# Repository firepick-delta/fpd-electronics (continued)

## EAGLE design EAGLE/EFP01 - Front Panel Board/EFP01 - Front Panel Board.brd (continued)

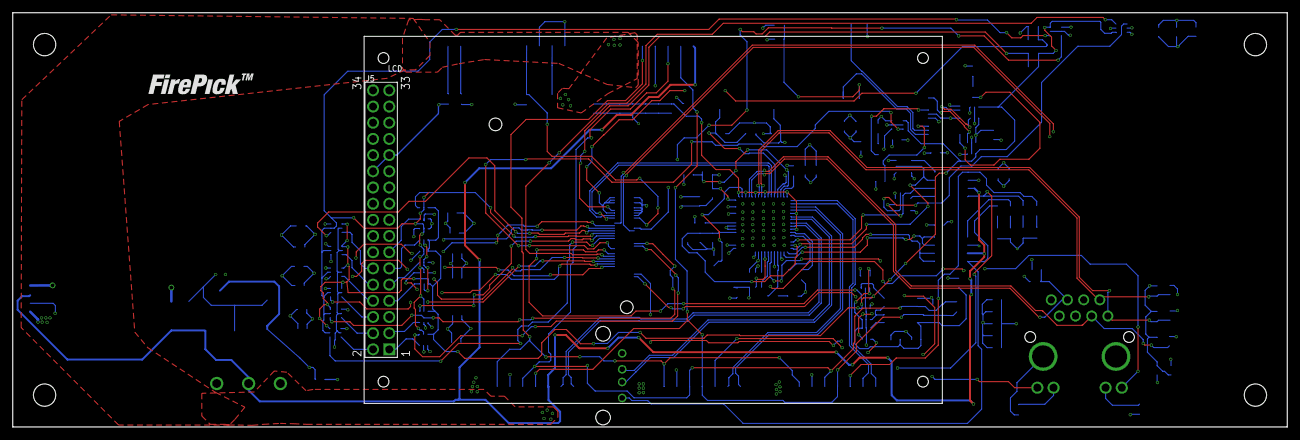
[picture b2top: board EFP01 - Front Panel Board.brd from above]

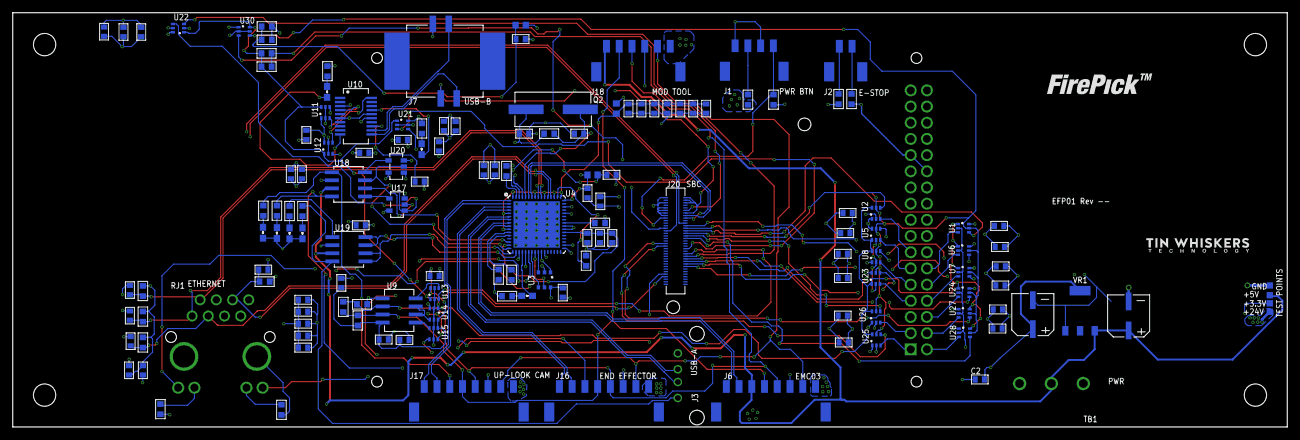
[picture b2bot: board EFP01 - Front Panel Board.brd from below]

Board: 4 copper layers, 200.0 x 65.0 mm, 151 parts (149 on the bottom side), 111 nets.

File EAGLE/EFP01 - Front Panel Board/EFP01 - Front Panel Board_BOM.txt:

Mfg Part Num	Description	Qty:	Price (USD):	Part References	Mfg Name	Distr.	DK P/N	Notes:
EFP01	Front Panel PCB	1	-	EFP01	Tin Whiskers Tech	-	-	-
-	PCB, Bare, FR-4, 0.062”, 4-Layer	1		-	HQPCB	-	-	-
GMK107BJ104KAHT	Capacitor: 0.1uF, 35V, 10%, X5R	50		C1, C2, C5, C6, C7, C8, C9, C10, C13, C14, C15, C16, C17, C18, C19, C20, C21, C22, C23, C27, C28, C29, C33, C34, C35, C36, C37, C38, C39, C40, C41, C42, C43, C44, C45, C46, C47, C48, C49, C60, C74, C79, C80, C81, C82, C84, C85, C24, C25, C77	Taiyo Yuden	ANY	587-3357-2-ND 	
RC0603JR-070RL	Resistor: 0.0 Ohm, 0.1W, 0%	1		R36	Yageo	ANY	311-0.0GRCT-ND	
RL0603FR-070R1L	Resistor: 0.1 Ohm, 0.1W, 1%	2		R15, R57	Yageo	ANY	311-.1QTR-ND	
UMK107AB7105KA-T	Capacitor, 1uF, 50V, 10%	1		C73	Taiyo Yuden	ANY	587-3247-1-ND	
RC0603FR-071KL	Resistor: 1 kOhm, 0.1W, 1%	2		R49, R50	Yageo	ANY	311-1.00KHRCT-ND	
RC0603FR-071ML	Resistor: 1 Mohm, 0.1W, 5%	1		R11	Yageo	ANY	311-1.00MHRCT-ND	
RC0603FR-074K7L	Resistor: 4.7 kOhm, 0.1W, 5%	1		R1	Yageo	ANY	311-4.70KHRTR-ND	
GRM188C81E475KE11D	Capacitor: 4.7 uF, 25V, 10%, X6S	2		C61, C83	Murata	ANY	490-7199-1-ND	
RC0603FR-0710KL	Resistor: 10 kOhm, 0.1W, 1%	3		R2, R14, R48	Yageo	ANY	311-10.0KHRCT-ND	
GRM188R71H103KA01D	Capacitor: 10nF, 50V, 10%, X7R	1		C78	Murata	ANY	490-1512-1-ND	
EMVH350ADA100MF60G	Capacitor, AL-Electrolytic, 10uF, 35V, 20%	2		C3, C4	United Chemi-Con	ANY	565-2310-2-ND	
RC0603FR-0712K4L	Resistor: 12.4 kOhm, 0.1W, 1%	1		R13	Yageo	ANY	311-12.4KHRCT-ND	
RC0603FR-0712KL	Resistor: 12.0 kOhm, 0.1W, 1%	1		R35	Yageo	ANY	311-12.0KHRCT-ND	
GCM1885C1H180JA16D	Capacitor: 18pF, 50V, 5%, C0G	4		C26, C30, C31, C32	Murata	ANY	490-6046-2-ND	
HCM4925000000MABJ	Crystal Oscillator: 25MHz, 18pF, 30PPM	1		Q2	Citizen FM	ANY	300-6148-2-ND	
C0603C330K5GACTU	Capacitor: 33 pF, 50V, C0G, 10%	2		C11, C12	Kemet	ANY	399-7897-2-ND	
RC0603FR-0749R9L	Resistor: 49.9Ohms, 0.1W, 1%	4		R22, R30, R31, R32	Yageo	ANY	311-49.9HRTR-ND	
74LVC1T45GW,125	Logic Shifter, Bidirectional, 3-State	20		U1, U2, U5, U6, U7, U8, U11, U12, U13, U14, U15, U21, U22, U23, U24, U25, U26, U27, U28, U30	NXP	ANY	568-5461-2-ND	
93LC66A-I/SN	EEPROM, 4KBIT, 2MHZ	1		U3	Microchip Tech.	ANY	93LC66A-I/SN-ND	
BLM18AG121SN1D	Ferrite Bead, Filter	3		FB1, FB3, FB4	Murata	ANY	490-1011-2-ND	
RC0603FR-07100RL	Resistor: 100 Ohm, 0.1W, 1%	1		R51	Yageo	ANY	311-100HRCT-ND	
RC0603FR-07270RL	Resistor: 270 Ohm, 0.1W, 1%	2		R53, R54	Yageo	ANY	311-270HRCT-ND	
RC0603FR-07330RL	Resistor: 330Ohm, 0.1W, 5%	3		R10, R33, R34	Yageo	ANY	311-330HRTR-ND	
RC0603FR-07511RL	Resistor: 511 Ohm, 0.1W, 1%	4		R37, R52, R55, R56	Yageo	ANY	311-511HRCT-ND	
RC0603FR-07825RL	Resistor: 825 Ohm, 0.1W, 1%	1		R12	Yageo	ANY	311-825HRCT-ND	
OSTTH030160	TERM BLOCK PLUG 3POS 90DEG 5MM	1		TB1	Onshore Technology	ANY	ED2656-ND	
RC0603JR-070RL	Resistor: 0.0 Ohm, 0.1W, 0%	2		R16, R58	Yageo	ANY	311-0.0GRCT-ND	
S2B-PH-SM4-TB(LF)(SN)	Connector: 2.0mm (JST), SMT, R/A, 2-POS(M)	1		J2	JST	ANY	455-1749-1-ND	
FT231XS-R	IC USB SERIAL FULL UART 20SSOP	1		U10	FTDI	ANY	768-1129-1-ND	
SML-D12M8WT86	LED: YW/GN, Diffused, 2.2V, 20mA	7		LED8, LED9, LED10, LED11, LED12, LED13, LED14	Rohm	ANY	511-1578-1-ND	
HR911105A	Connector: Ethernet, MagJack, RJ-45, LED+SHD	1		RJ1	HanRun	ANY	*	
DF40HC(3.0)-70DS-0.4V(51)	Connector: 0.4mm, 70-pin, Receptacle, SMT	1		J20	Hirose	ANY	DF40HC(3.0)-70DS-0.4V(51)-ND	
LAN9514-JZX	USB, Ethernet Controller	1		U4	Microchip Tech.	ANY	638-1087-ND	
TSW-117-07-T-D	Connector: Header, 0.1ﾔ, 34-Pin, Male, SN	1		J5	Samtec	ANY	SAM1034-17-ND	
LMS8117AMP-3.3/NOPB	Voltage Reg(LDO): Vi=15V, Vo=3.3V, I=1A	1		VR1	Texas Instruments	ANY	LMS8117AMP-3.3/NOPBCT-ND	
MIC2026-1YM	Power Distribution Switch, 2-Channel	2		U18, U19	Micrel Inc	ANY	576-1059-1-ND	
SN74LVC1G32DBVR	Logic Gate: OR, 1-CH, SOT23-5	2		U17, U20	Texas Instruments	ANY	296-9847-1-ND	
RC0603JR-070RL	Resistor: 0.0 Ohm, 0.1W, 0%	1		R3	Yageo	ANY	311-0.0GRCT-ND	
S4B-PH-SM4-TB(LF)(SN)	Connector: 2.0mm (JST), SMT, R/A, 4-POS(M)	1		J1	JST	ANY	455-1751-1-ND	
B6B-PH-SM4-TB(LF)(SN)	Connector: 2.0mm (JST), SMT, VRT, 6-POS(M)	1		J18	JST	ANY	455-1738-1-ND	
B8B-PH-SM4-TB(LF)(SN)	Connector: 2.0mm (JST), SMT, VRT, 8-POS(M)	3		J6, J16, J17	JST	ANY	455-1740-1-ND	
SP3485	Transceiver: RS-485 Chip	1		U9	EXAR	ANY	1016-1817-1-ND	
1734085-1	Connector: USB, A-Type, Thru-Hole, VRT, 2.0	1		J3	TE Connectivity	ANY	A114935-ND	
1734517-1	Connector: USB, B-Type, SMT, VRT, 2.0	1		J7	TE Connectivity	ANY	A111053CT-ND

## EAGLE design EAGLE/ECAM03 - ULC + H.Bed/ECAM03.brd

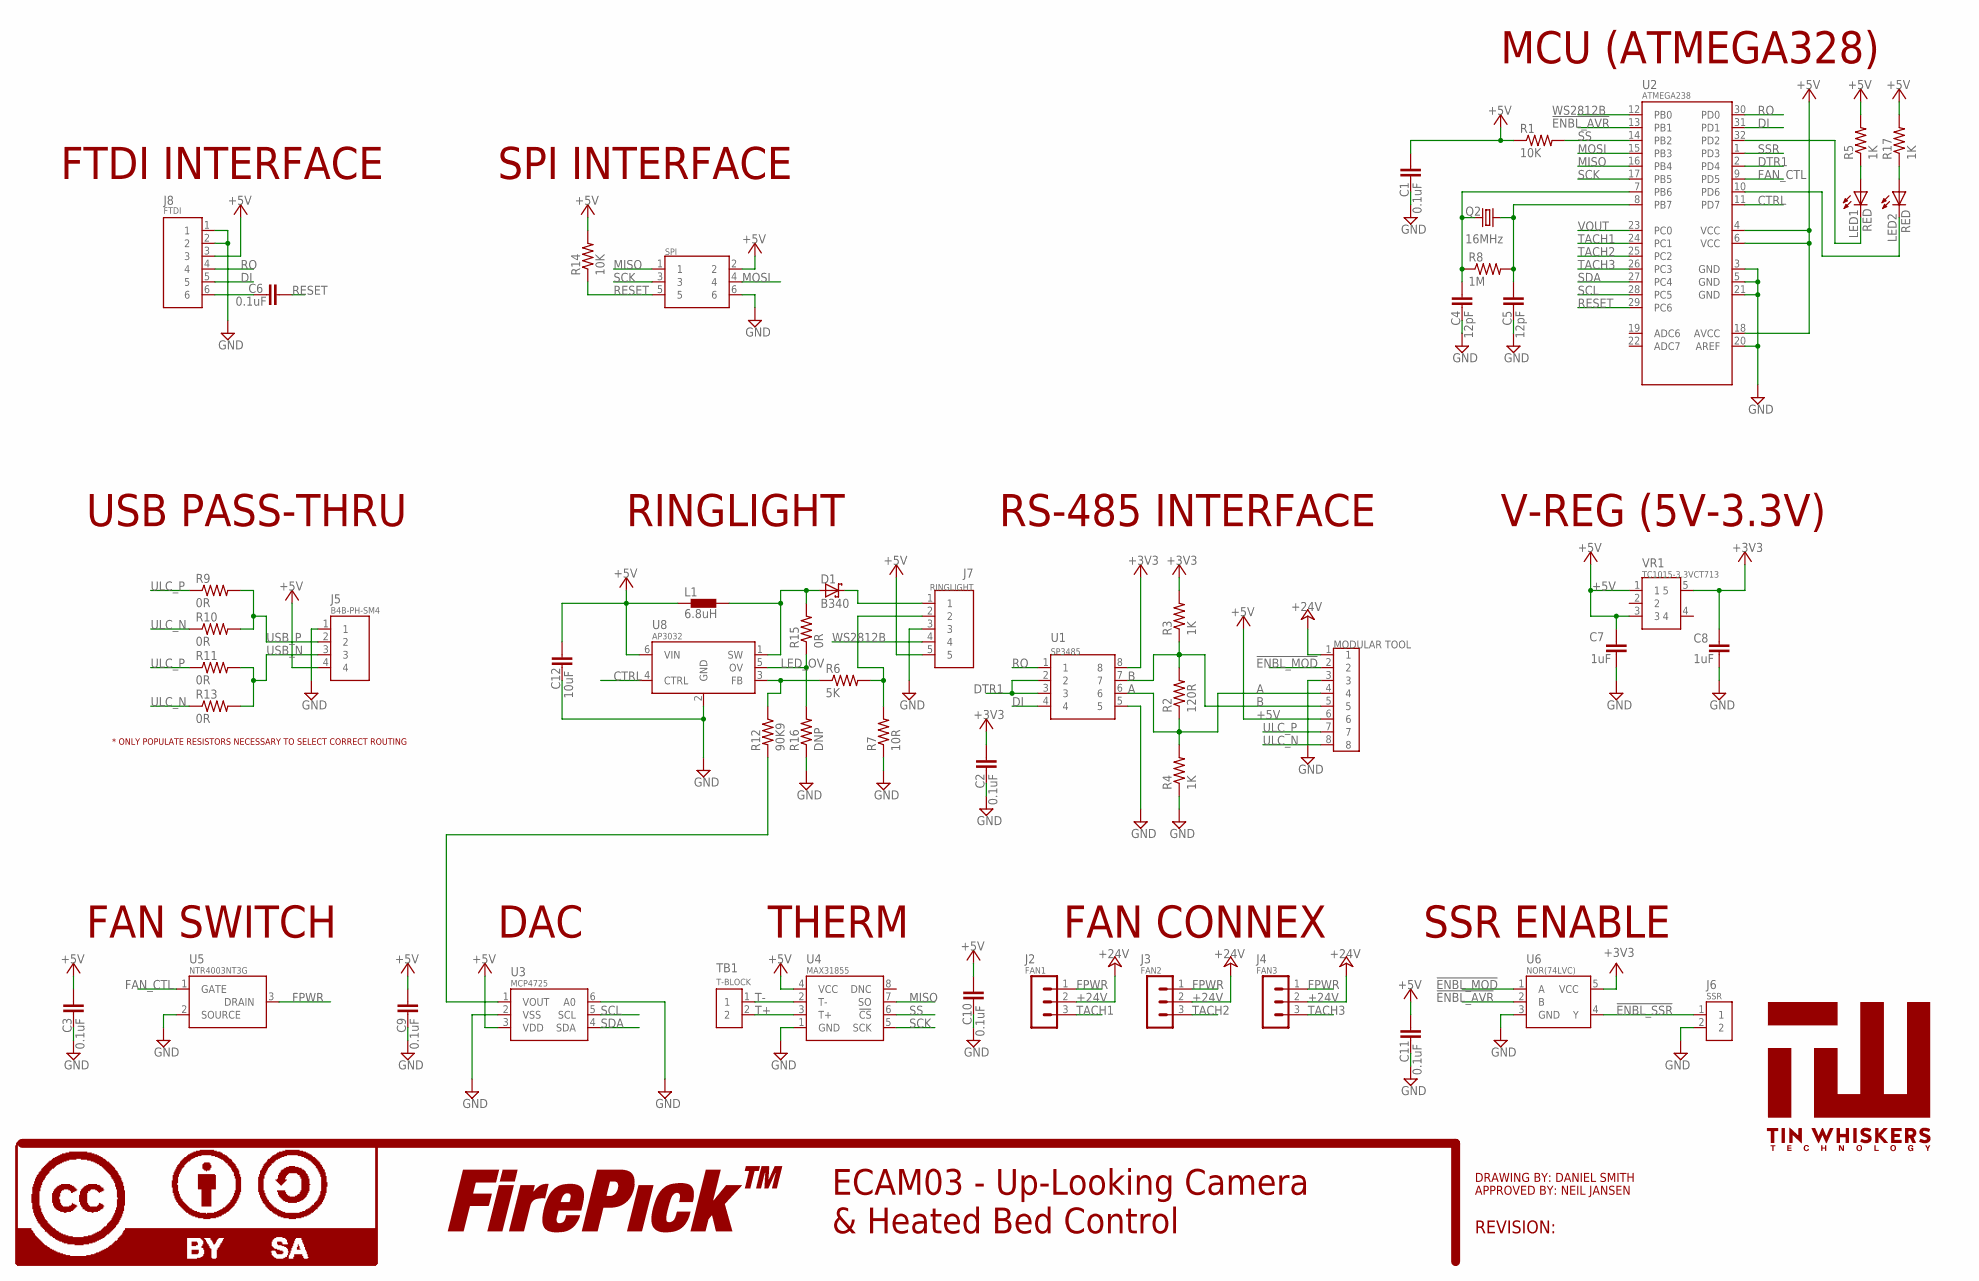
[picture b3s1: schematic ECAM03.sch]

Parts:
C1, C2, C3, C9, C10, C11: 0.1uF; C0603
C4, C5: 12pF; C0603; PARTNO GRM1885C1H120FA01J
C6: 0.1uF; C0603; PARTNO UMK107B7104KA-T
C7, C8: 1uF; C0603; PARTNO UMK107AB7105KA-T
C12: 10uF; C0603; PARTNO GRM188R61C106MA73D
D1: B340; DIO-SMA; PARTNO B340A-13-F
J1: MODULAR TOOL; CONN-JST-PH-2.0MM-8P-SMT-RA; PARTNO S8B-PH-SM4-TB(LF)(SN)
J2: FAN1; CONN-MOLEX-KK-3PIN; PARTNO 22232031
J3: FAN2; CONN-MOLEX-KK-3PIN; PARTNO 22232031
J4: FAN3; CONN-MOLEX-KK-3PIN; PARTNO 22232031
J5: B4B-PH-SM4; CON-JST-PH-2.0MM-4P-SMT-VRT; PARTNO B4B-PH-SM4-TB(LF)(SN)
J6: SSR; CON-HDR-2POS-MALE; PARTNO 68000-102HLF
J7: RINGLIGHT; CON-JST-PH-2.0MM-5P-SMT-VRT; PARTNO B5B-PH-SM4-TB(LF)(SN)
J8: FTDI; CON-HDR-6POS-MALE; PARTNO S6B-PH-SM4-TB(LF)(SN)
J9: SPI; CON-HDR-2X3P; PARTNO 67996-206HLF
L1: 6.8uH; 0603; PARTNO BRL1608T6R8M
LED1, LED2: RED; LED0603
LOGO1: LOGO-CC-BY-SALARGE; LOGO-CC-BY-SA
LOGO2: LOGO-FIREPICKLARGE; LOGO-FIREPICK
Q2: 16MHz; HC-49/U-S; PARTNO HCM4916000000ABJT
R1, R14: 10K; R0603; PARTNO RC0603FR-0710KL
R2: 120R; R0603; PARTNO RC0603FR-07120RL
R3, R4: 1K; R0603; PARTNO RC0603FR-071KL
R5, R17: 1K; R0603
R6: 5K; R0603; PARTNO RC0603FR-074K99L
R7: 10R; R1206; PARTNO RC1206FR-0710RL
R8: 1M; R0603; PARTNO RC0603FR-071ML
R9, R10, R11, R13, R15: 0R; R0603; PARTNO RC0603JR-070RL
R12: 90K9; R0603; PARTNO RC0603FR-0790K9L
R16: DNP; R0603; PARTNO RC0603JR-070RL
TB1: T-BLOCK; TBLOCK-2-5MM-OSTTH020160; PARTNO OSTTH020160
U1: SP3485; SOICN-8; PARTNO SP3485
U2: ATMEGA238; 32-TQF(ATMEGA); PARTNO ATMEGA328-AUR
U3: MCP4725; SOT-23-6; PARTNO MCP4725A0T-E/CH
U4: MAX31855; SOICN-8; PARTNO MAX31855KASA+
U5: NTR4003NT3G; SOT-23-3; PARTNO NTR4003NT3G
U6: NOR(74LVC); SOT-23-5; PARTNO SN74LVC1G02DBVR
U8: AP3032; SOT-23-6; PARTNO AP3032KTR-G1
U$1: TIN-WHISKERSTSTOP; TIN-WHISKERS-TSTOP; PARTNO *
VR1: TC1015-3.3VCT713; SOT-23-5; PARTNO TC1015-3.3VCT713

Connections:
!ENBL_AVR: U2.13 (PB1), U6.2 (B)
!ENBL_MOD: J1.2, U6.1 (A)
!ENBL_SSR: J6.1, U6.4 (Y)
+3V3: C2.2, C8.2, R3.2, U1.8, U6.5 (VCC), VR1.5
+5V: C1.2, C3.2, C7.2, C9.2, C10.2, C11.2, C12.2, J1.6, J5.4, J7.5, J8.3, J9.2, L1.1, R1.1, R5.2, R14.2, R17.2, U2.4 (VCC), U2.6 (VCC), U2.18 (AVCC), U3.3 (VDD), U4.4 (VCC), U8.6 (VIN), VR1.1, VR1.3
+24V: J1.1, J2.2, J3.2, J4.2
A: J1.4, R2.1, R4.2, U1.6
B: J1.5, R2.2, R3.1, U1.7
CTRL: U2.11 (PD7), U8.4 (CTRL)
DI: J8.5, U1.4, U2.31 (PD1)
DTR1: U1.2, U1.3, U2.2 (PD4)
FAN_CTL: U2.9 (PD5), U5.1 (GATE)
FPWR: J2.1, J3.1, J4.1, U5.3 (DRAIN)
GND: C1.1, C2.1, C3.1, C4.1, C5.1, C7.1, C8.1, C9.1, C10.1, C11.1, C12.1, J1.3, J5.1, J6.2, J7.3, J8.1, J8.2, J9.6, R4.1, R7.1, R16.1, U1.5, U2.3 (GND), U2.5 (GND), U2.20 (AREF), U2.21 (GND), U3.2 (VSS), U3.6 (A0), U4.1 (GND), U5.2 (SOURCE), U6.3 (GND), U8.2 (GND)
LED_+: D1.NEG (C), J7.1
LED_-: J7.2, R6.2, R7.2
LED_FB: R6.1, R12.1, U8.3 (FB)
LED_OV: R15.1, R16.2, U8.5 (OV)
LED_SW: D1.POS (A), L1.2, R15.2, U8.1 (SW)
MISO: J9.1, U2.16 (PB4), U4.7 (SO)
MOSI: J9.4, U2.15 (PB3)
unnamed: LED2.A, R17.1
unnamed: LED1.A, R5.1
unnamed: LED1.C, U2.32 (PD2)
unnamed: LED2.C, U2.10 (PD6)
unnamed: R12.2, U3.1 (VOUT)
unnamed: C6.1, J8.6
RESET: C6.2, J9.5, R14.1, U2.29 (PC6)
RO: J8.4, U1.1, U2.30 (PD0)
SCK: J9.3, U2.17 (PB5), U4.5 (SCK)
SCL: U2.28 (PC5), U3.5 (SCL)
SDA: U2.27 (PC4), U3.4 (SDA)
SS: R1.2, U2.14 (PB2), U4.6 (!CS)
SSR: U2.1 (PD3)
T+: TB1.2, U4.3 (T+)
T-: TB1.1, U4.2 (T-)
TACH1: J2.3, U2.24 (PC1)
TACH2: J3.3, U2.25 (PC2)
TACH3: J4.3, U2.26 (PC3)
ULC_N: J1.8, R10.1, R13.1
ULC_P: J1.7, R9.1, R11.1
USB_N: J5.3, R11.2, R13.2
USB_P: J5.2, R9.2, R10.2
VOUT: U2.23 (PC0)
WS2812B: J7.4, U2.12 (PB0)
XTAL1: C4.2, Q2.1, R8.1, U2.7 (PB6)
XTAL2: C5.2, Q2.2, R8.2, U2.8 (PB7)

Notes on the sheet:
ECAM03 - Up-Looking Camera & Heated Bed Control
DRAWING BY: DANIEL SMITH
APPROVED BY: NEIL JANSEN
REVISION:
MCU (ATMEGA328)
RS-485 INTERFACE
RINGLIGHT
USB PASS-THRU
* ONLY POPULATE RESISTORS NECESSARY TO SELECT CORRECT ROUTING
DAC
THERM
FAN CONNEX
FAN SWITCH
SSR ENABLE
V-REG (5V-3.3V)
FTDI INTERFACE
SPI INTERFACE
SPI

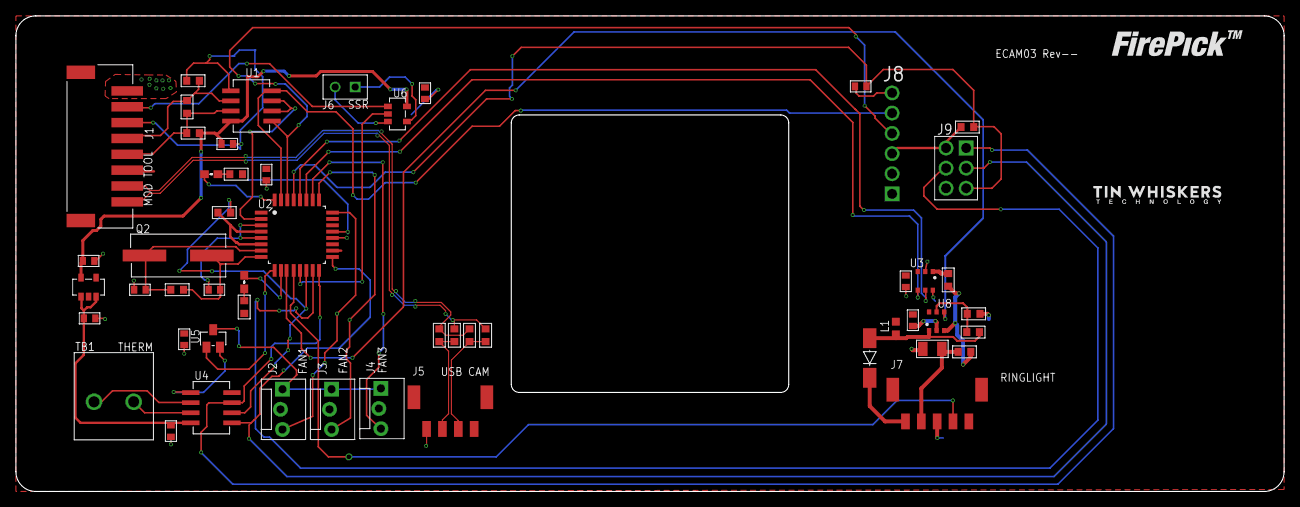
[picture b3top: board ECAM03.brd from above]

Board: 4 copper layers, 160.0 x 60.0 mm, 55 parts (1 on the bottom side), 45 nets.

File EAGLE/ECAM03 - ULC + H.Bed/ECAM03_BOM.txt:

Mfg Part Num	Description	QTY:	REFDES	Price (USD):	Mfr:	Distr:	Vendor Part Num	Notes:
ECAM03	Up-Looking Camera & Heated Bed PCB	1	ECAM03	-	Tin Whiskers Tech	-	-	
-	PCB, Bare, FR-4 0.062” Thickness	1	-		HQPCB	-	-	
UMK107B7104KA-T	Capacitor: 0.1uF, 50V, 10%, X7R	1	C6		Taiyo Yuden	ANY	587-1243-1-ND	
RC0603JR-070RL	Resistor: 0.0 Ohm, 0.1W, 0%	5	R9, R10, R11, R13, R15		Yageo	ANY	311-0.0GRCT-ND	
RC0603FR-071KL	Resistor: 1 kOhm, 0.1W, 1%	2	R3, R4		Yageo	ANY	311-1.00KHRCT-ND	
RC0603FR-071ML	Resistor: 1 Mohm, 0.1W, 5%	1	R8		Yageo	ANY	311-1.00MHRCT-ND	
UMK107AB7105KA-T	Capacitor, 1uF, 50V, 10%	2	C7, C8		Taiyo Yuden	ANY	587-3247-1-ND	
RC0603FR-074K99L	Resistor: 4.99 kOhm, 0.1W, 1%	1	R6		Yageo	ANY	311-4.99KHRCT-ND	
BRL1608T6R8M	Inductor: 6.8uH, 20%, SMT	1	L1		Taiyo Yuden	ANY	587-2902-1-ND	
RC0603FR-0710KL	Resistor: 10 kOhm, 0.1W, 1%	2	R1, R14		Yageo	ANY	311-10.0KHRCT-ND	
RC1206FR-0710RL	Resistor: 10 Ohm, 0.25W, 1%	1	R7		Yageo	ANY	311-10.0FRCT-ND	
GRM188R61C106MA73D	Capacitor: 10uF, 16V, 20%	1	C12		Murata	ANY	490-7201-1-ND	
GRM1885C1H120FA01J	Capacitor: 12pF, 50V, 1%, C0G	2	C4, C5		Murata	ANY	490-10705-1-ND	
HCM4916000000ABJT	Crystal Oscillator: 16MHz, 18pF, SMD	1	Q2		Citizen FM	ANY	300-6134-1-ND	
RC0603FR-0790K9L	Resistor: 90.9 kOhm, 0.1W, 1%	1	R12		Yageo	ANY	311-90.9KHRCT-ND	
RC0603FR-07100RL	Resistor: 100 Ohm, 0.1W, 1%	1	R2		Yageo	ANY	311-100HRCT-ND	
AP3032KTR-G1	Driver: LED, Regulator/Dimmer	1	U8		Diodes Incorporated	ANY	AP3032KTR-G1DICT-ND	
ATMEGA328-AUR	Microprocessor: AVR, 20MHz, 8-Bit Core	1	U2		Atmel	ANY	ATMEGA328-AURCT-ND	
B4B-PH-SM4-TB(LF)(SN)	Connector: 2.0mm (JST), SMT, VRT, 4-POS(M)	1	J5		JST	ANY	455-1736-1-ND	
B340A-13-F	Diode: Rectifier (Schottky), 3A, 40V	1	D1		Diodes Incorporated	ANY	FB340A-FDICT-ND	
RC0603JR-070RL	Resistor: 0.0 Ohm, 0.1W, 0%	1	R16		Yageo	ANY	311-0.0GRCT-ND	
22232031	CONN HEADER 3POS .100 VERT TIN	3	J2, J3, J4		Molex Inc	ANY	WM4201-ND	
S6B-PH-SM4-TB(LF)(SN)	Connector: 2.0mm (JST), SMT, R/A, 6-POS(M)	1	J8		JST	ANY	455-1753-1-ND	
MAX31855KASA+	Converter: Thermocouple-Digital, SPI	1	U4		Maxim Integrated	ANY	MAX31855KASA+-ND	
MCP4725A0T-E/CH	DAC: 12BIT, I2C	1	U3		Microchip Tech.	ANY	MCP4725A0T-E/CHCT-ND	
S8B-PH-SM4-TB(LF)(SN)	Connector: 2.0mm (JST), SMT, R/A, 8-POS(M)	1	J1		JST	ANY	455-1755-1-ND	
SN74LVC1G02DBVR	Logic Gate: NOR, 1-CH, 2-Input, 	1	U6		Texas Instruments	ANY	296-11597-1-ND	
NTR4003NT3G	MOSFET: N-Ch, 30V, 500mA	1	U5		ON Semiconductor	ANY	NTR4003NT3GOSCT-ND	
B5B-PH-SM4-TB(LF)(SN)	Connector: 2.0mm (JST), SMT, VRT, 5-POS(M)	1	J7		JST	ANY	455-1737-1-ND	
SP3485	Transceiver: RS-485 Chip	1	U1		EXAR	ANY	1016-1817-1-ND	
67996-206HLF	Connector: Header, 0.1ﾔ, 6-Pin, Male, Thru-Hole	1	J9		FCI	ANY	609-3210-ND	
68000-102HLF	Connector: Header, 0.1ﾔ, 2-Pin, Male, Thru-Hole	1	J6		FCI	ANY	609-3500-ND	
OSTTH020160	Terminal Block: 2-POS, 5MM Pitch, R/A, 14-22AWG	1	TB1		On Shore Technology Inc	ANY	ED2655-ND	
TC1015-3.3VCT713	Voltage Reg(LDO): Vi=6V, Vo=3.3V, Io=0.1A	1	VR1		Microchip Tech.	ANY	TC1015-3.3VCT713CT-ND

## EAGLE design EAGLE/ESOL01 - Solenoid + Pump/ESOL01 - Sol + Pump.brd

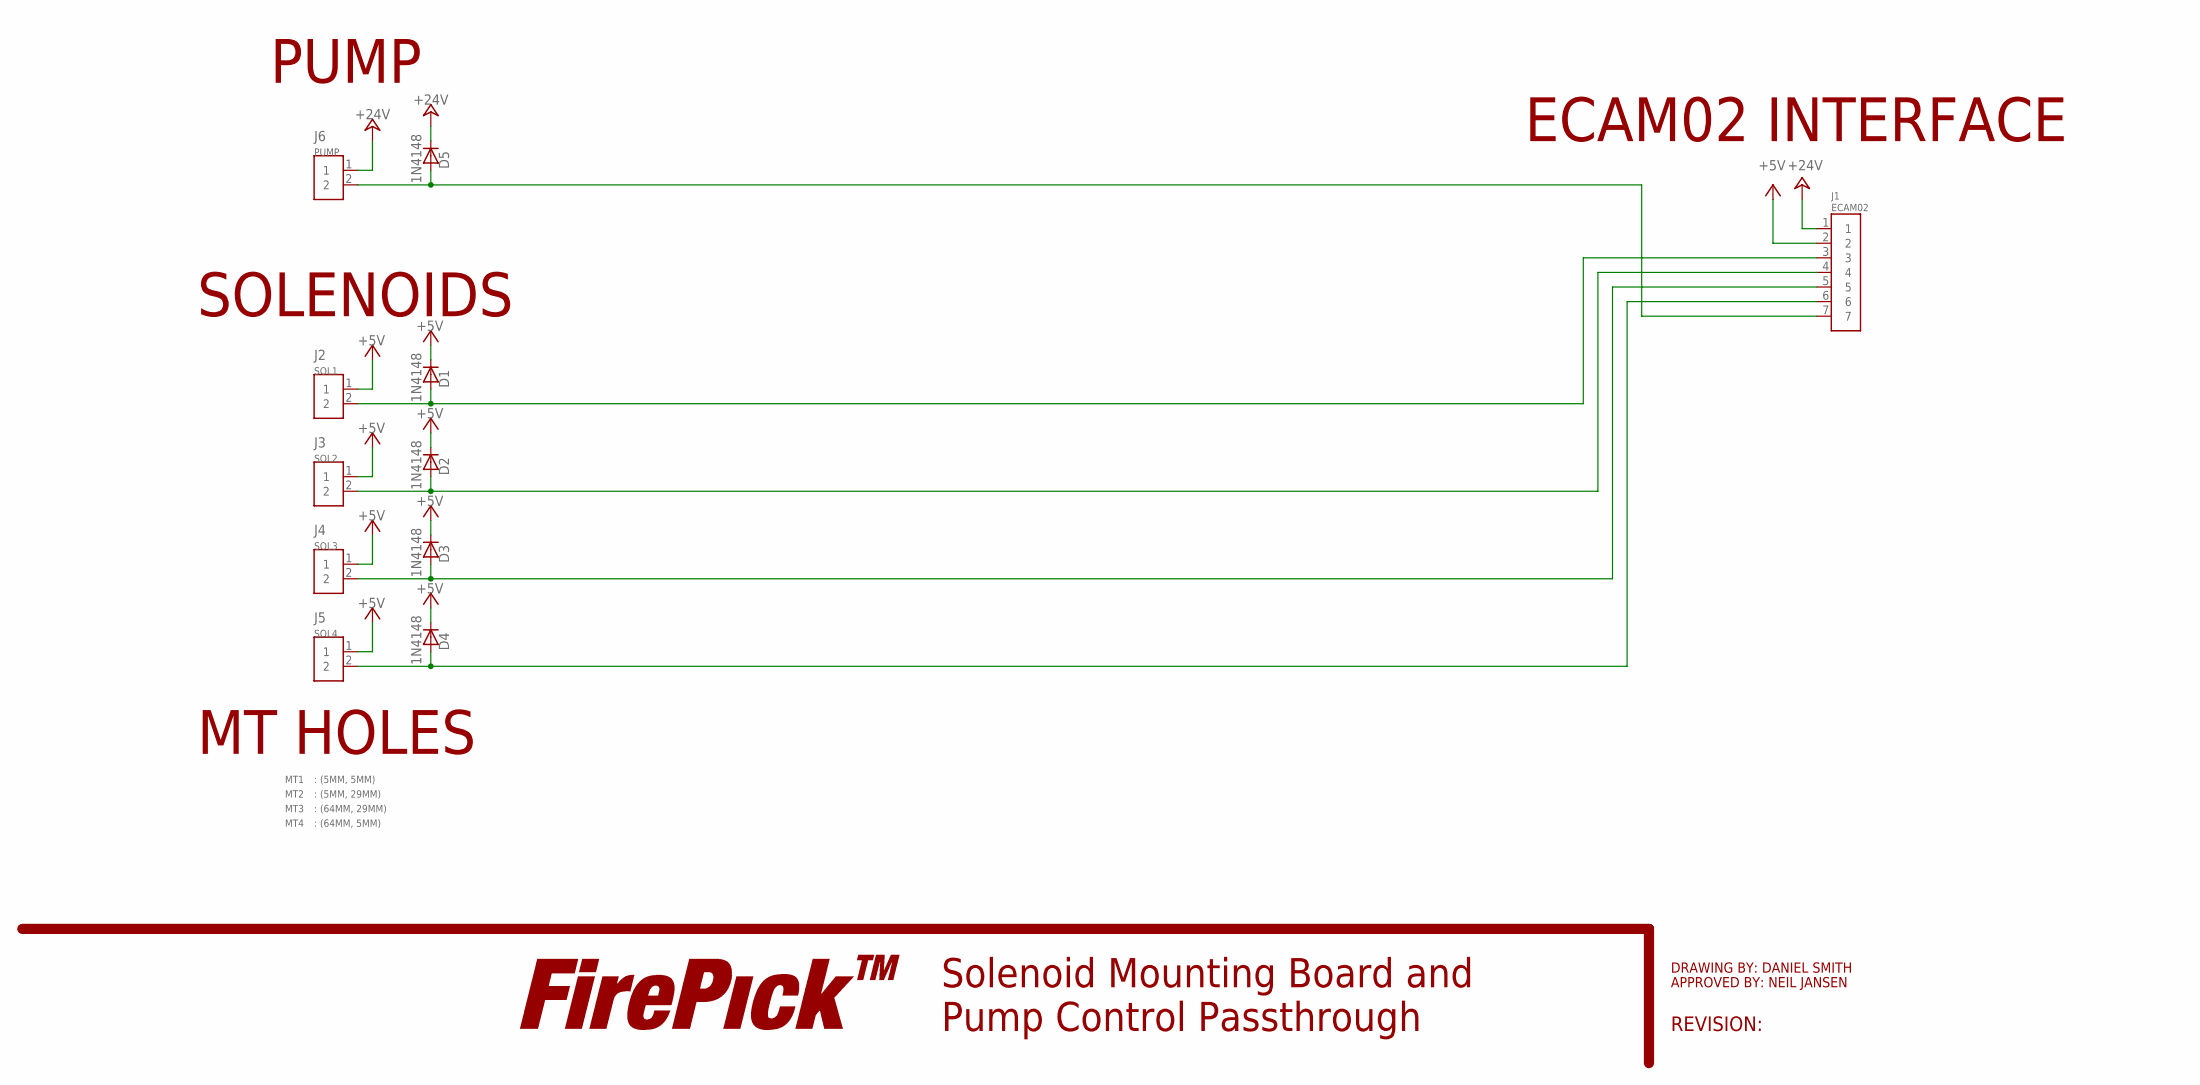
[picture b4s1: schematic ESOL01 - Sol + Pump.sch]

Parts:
D1, D2, D3, D4, D5: 1N4148; SOD-323
J1: ECAM02; CON-JST-PH-2.0MM-7P-SMT-VRT
J2: SOL1; HOLEX2
J3: SOL2; HOLEX2
J4: SOL3; HOLEX2
J5: SOL4; HOLEX2
J6: PUMP; CON-JST-PH-2.0MM-2P-SMT-VRT
LOGO2: LOGO-FIREPICKLARGE; LOGO-FIREPICK
MT1: : (5MM, 5MM); MTHOLE(M3)
MT2: : (5MM, 29MM); MTHOLE(M3)
MT3: : (64MM, 29MM); MTHOLE(M3)
MT4: : (64MM, 5MM); MTHOLE(M3)

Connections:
+5V: D1.NEG (C), D2.NEG (C), D3.NEG (C), D4.NEG (C), J1.2, J2.1, J3.1, J4.1, J5.1
+24V: D5.NEG (C), J1.1, J6.1
unnamed: D1.POS (A), J1.3, J2.2
unnamed: D2.POS (A), J1.4, J3.2
unnamed: D3.POS (A), J1.5, J4.2
unnamed: D4.POS (A), J1.6, J5.2
unnamed: D5.POS (A), J1.7, J6.2

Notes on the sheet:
PUMP
SOLENOIDS
ECAM02 INTERFACE
Solenoid Mounting Board and Pump Control Passthrough
DRAWING BY: DANIEL SMITH
APPROVED BY: NEIL JANSEN
REVISION:
MT HOLES

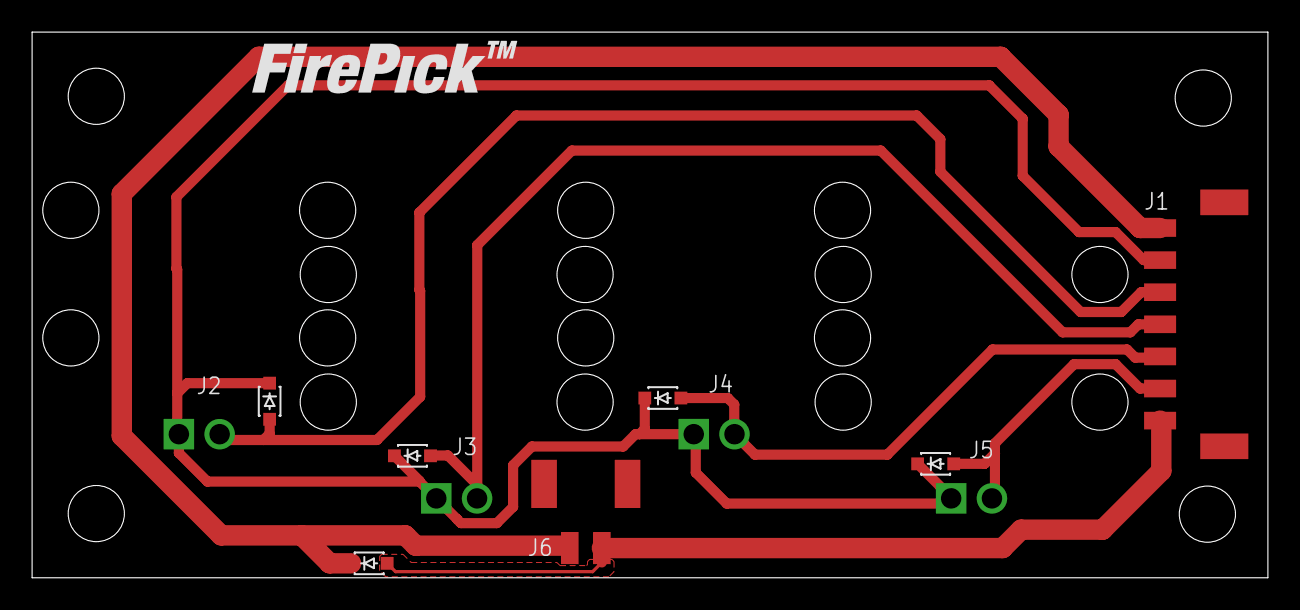
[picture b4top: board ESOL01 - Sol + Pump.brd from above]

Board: 4 copper layers, 77.0 x 34.0 mm, 16 parts (0 on the bottom side), 7 nets.

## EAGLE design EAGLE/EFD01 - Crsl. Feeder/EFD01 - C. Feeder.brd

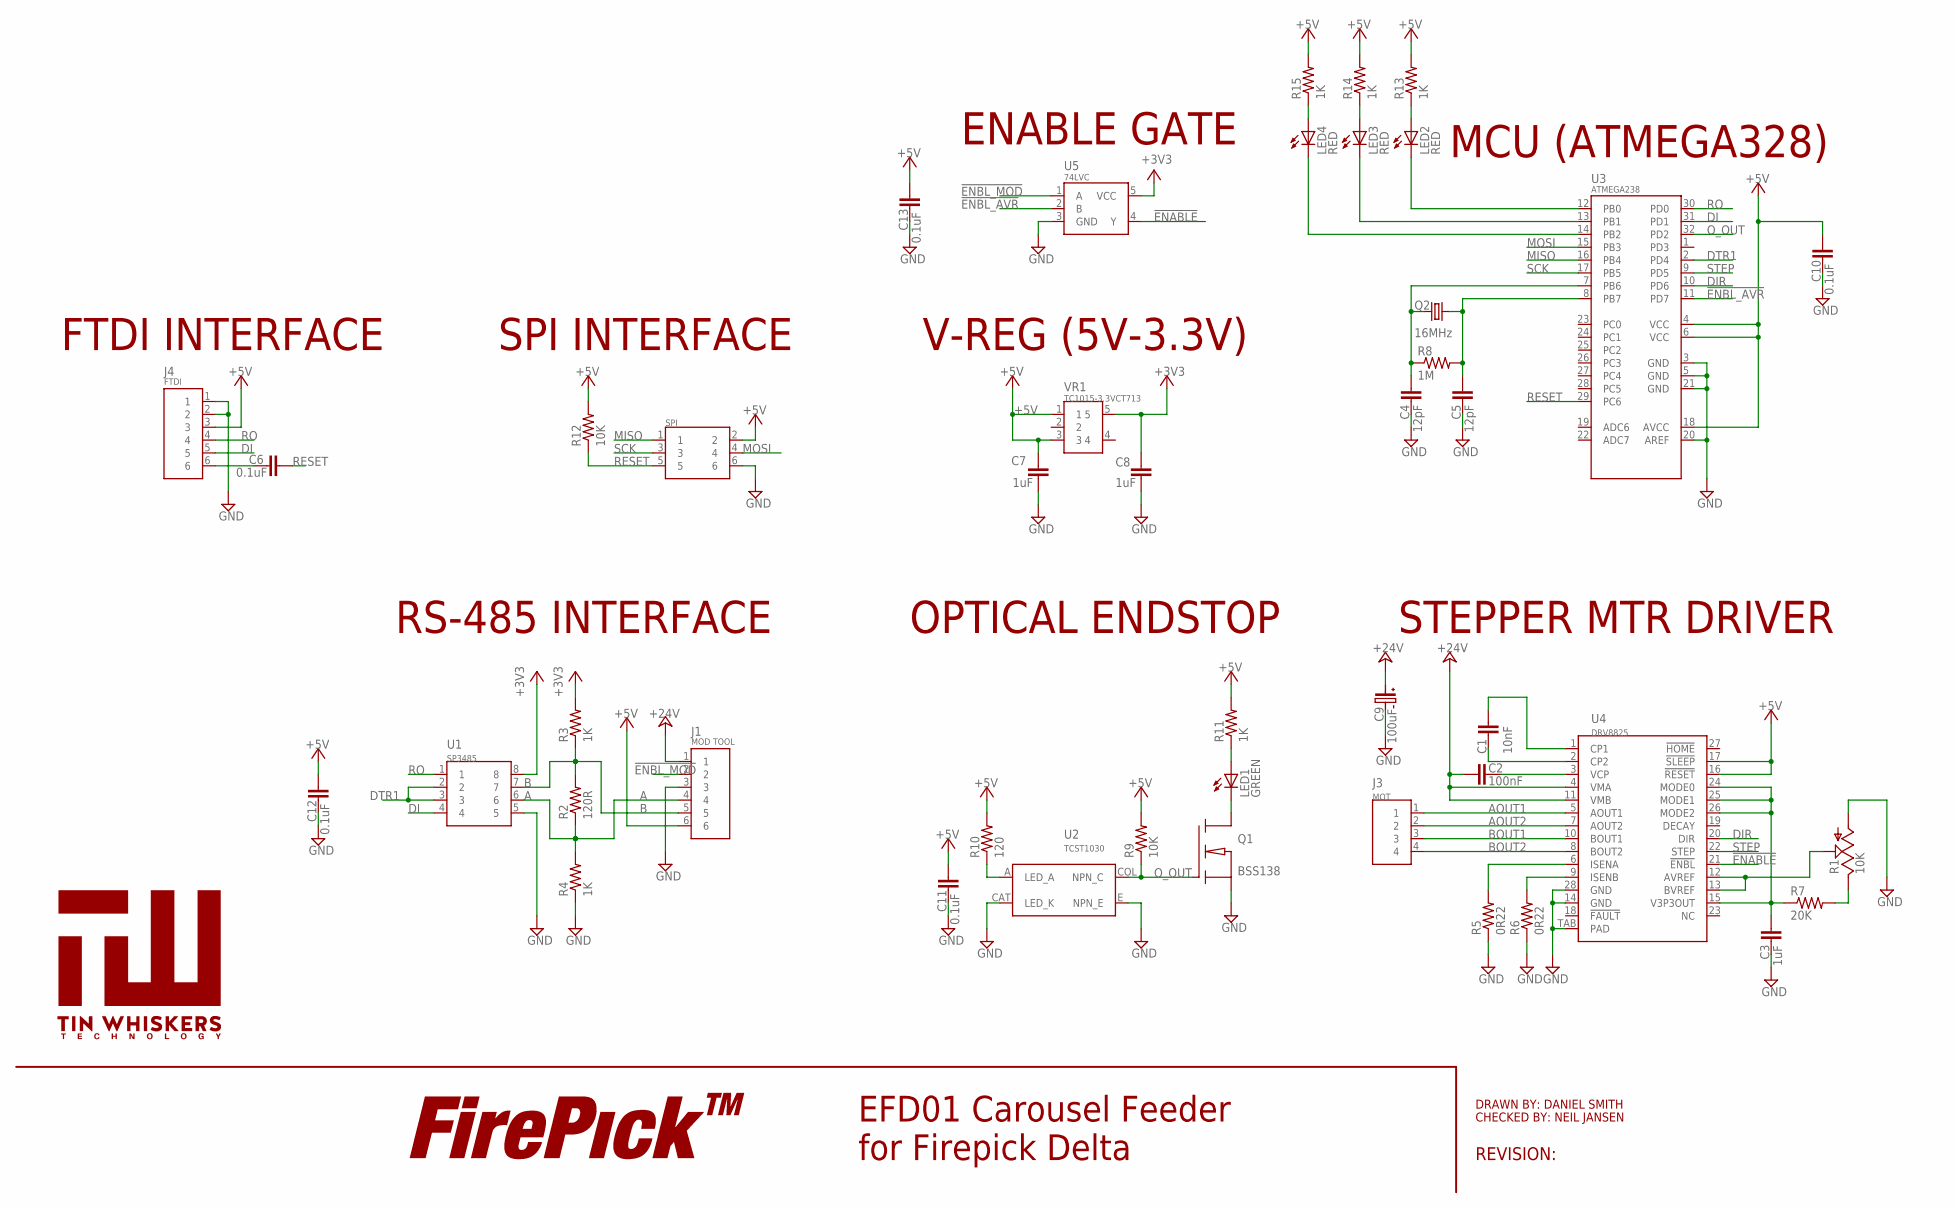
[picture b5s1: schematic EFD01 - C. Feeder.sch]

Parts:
C1: 10nF; C0603; PARTNO GRM188R71H103KA01D
C2: 100nF; C0603; PARTNO UMK107B7104KA-T
C3, C7, C8: 1uF; C0603; PARTNO UMK107AB7105KA-T
C4, C5: 12pF; C0603; PARTNO GRM1885C1H120FA01J
C6, C10, C11, C12, C13: 0.1uF; C0603; PARTNO UMK107B7104KA-T
C9: 100uF; C-SMD-6.3MM; PARTNO EMVA500ADA101MHA0G
J1: MOD TOOL; CONN-JST-PH-2.0MM-6P-SMT-RA; PARTNO S6B-PH-SM4-TB(LF)(SN)
J2: SPI; CON-HDR-2X3P; PARTNO 67996-206HLF
J3: MOT; CONN-JST-PH-2.0MM-4P-SMT-RA; PARTNO S4B-PH-SM4-TB(LF)(SN)
J4: FTDI; CON-HDR-6POS-MALE; PARTNO S6B-PH-SM4-TB(LF)(SN)
LED1: GREEN; LED0603; PARTNO SML-D12M8WT86
LED2, LED3, LED4: RED; LED0603; PARTNO SML-D12M8WT86
LOGO2: LOGO-FIREPICKLARGE; LOGO-FIREPICK
Q1: BSS138; SOT-23-3; PARTNO BSS138
Q2: 16MHz; HC-49/U-S; PARTNO HCM4916000000ABJT
R1: 10K; TC33X-2; PARTNO TC33X-2-103E
R2: 120R; R0603; PARTNO RC0603FR-07120RL
R3, R4, R11, R13, R14, R15: 1K; R0603; PARTNO RC0603FR-071KL
R5, R6: 0R22; R1206; PARTNO RL1206FR-7W0R22L
R7: 20K; R0603; PARTNO RC0603FR-0722KL
R8: 1M; R0603; PARTNO RC0603FR-071ML
R9, R12: 10K; R0603; PARTNO RC0603FR-0710KL
R10: 120; R0603; PARTNO RC0603FR-07120RL
U1: SP3485; SOICN-8; PARTNO SP3485
U2: TCST1030; PARTNO TCST1030
U3: ATMEGA238; 32-TQF(ATMEGA); PARTNO ATMEGA328-AUR
U4: DRV8825; 28-HSSOP; PARTNO DRV8825PWPR
U5: 74LVC; SOT-23-5; PARTNO SN74LVC1G32DBVR
U$1: TIN-WHISKERSSMALL; TIN-WHISKERS-SMALL; PARTNO *
VR1: TC1015-3.3VCT713; SOT-23-5; PARTNO TC1015-3.3VCT713

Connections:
!ENABLE: U4.21 (!ENBL), U5.4 (Y)
!ENBL_AVR: U3.11 (PD7), U5.2 (B)
!ENBL_MOD: J1.2, U5.1 (A)
+3V3: C8.2, R3.2, U1.8, U5.5 (VCC), VR1.5
+5V: C7.2, C10.2, C11.2, C12.2, C13.2, J1.6, J2.2, J4.3, R9.2, R10.2, R11.2, R12.2, R13.2, R14.2, R15.2, U3.4 (VCC), U3.6 (VCC), U3.18 (AVCC), U4.16 (!RESET), U4.17 (!SLEEP), VR1.1, VR1.3
+24V: C2.1, C9.POS, J1.1, U4.4 (VMA), U4.11 (VMB)
A: J1.4, R2.1, R4.2, U1.6
AOUT1: J3.1, U4.5 (AOUT1)
AOUT2: J3.2, U4.7 (AOUT2)
B: J1.5, R2.2, R3.1, U1.7
BOUT1: J3.3, U4.10 (BOUT1)
BOUT2: J3.4, U4.8 (BOUT2)
DI: J4.5, U1.4, U3.31 (PD1)
DIR: U3.10 (PD6), U4.20 (DIR)
DTR1: U1.2, U1.3, U3.2 (PD4)
GND: C3.1, C4.1, C5.1, C7.1, C8.1, C9.NEG, C10.1, C11.1, C12.1, C13.1, J1.3, J2.6, J4.1, J4.2, Q1.2 (S), R1.1 (A), R4.1, R5.1, R6.1, U1.5, U2.CAT (LED_K), U2.E (NPN_E), U3.3 (GND), U3.5 (GND), U3.20 (AREF), U3.21 (GND), U4.14 (GND), U4.28 (GND), U4.TAB (PAD), U5.3 (GND)
MISO: J2.1, U3.16 (PB4)
MOSI: J2.4, U3.15 (PB3)
unnamed: LED1.C, Q1.3 (D)
unnamed: R10.1, U2.A (LED_A)
unnamed: LED1.A, R11.1
unnamed: C1.2, U4.1 (CP1)
unnamed: C1.1, U4.2 (CP2)
unnamed: LED2.C, U3.12 (PB0)
unnamed: R5.2, U4.6 (ISENA)
unnamed: R6.2, U4.9 (ISENB)
unnamed: LED2.A, R13.1
unnamed: LED3.C, U3.13 (PB1)
unnamed: LED3.A, R14.1
unnamed: C3.2, R7.1, U4.15 (V3P3OUT), U4.24 (MODE0), U4.25 (MODE1), U4.26 (MODE2)
unnamed: R1.3 (E), R7.2
unnamed: R1.2 (S), U4.12 (AVREF), U4.13 (BVREF)
unnamed: C6.1, J4.6
unnamed: LED4.C, U3.14 (PB2)
unnamed: LED4.A, R15.1
O_OUT: Q1.1 (G), R9.1, U2.COL (NPN_C), U3.32 (PD2)
RESET: C6.2, J2.5, R12.1, U3.29 (PC6)
RO: J4.4, U1.1, U3.30 (PD0)
SCK: J2.3, U3.17 (PB5)
STEP: U3.9 (PD5), U4.22 (STEP)
VCP: C2.2, U4.3 (VCP)
XTAL1: C4.2, Q2.1, R8.1, U3.7 (PB6)
XTAL2: C5.2, Q2.2, R8.2, U3.8 (PB7)

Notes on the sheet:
STEPPER MTR DRIVER
MCU (ATMEGA328)
OPTICAL ENDSTOP
V-REG (5V-3.3V)
RS-485 INTERFACE
SPI INTERFACE
FTDI INTERFACE
EFD01 Carousel Feeder for Firepick Delta
DRAWN BY: DANIEL SMITH
CHECKED BY: NEIL JANSEN
REVISION:
ENABLE GATE
SPI

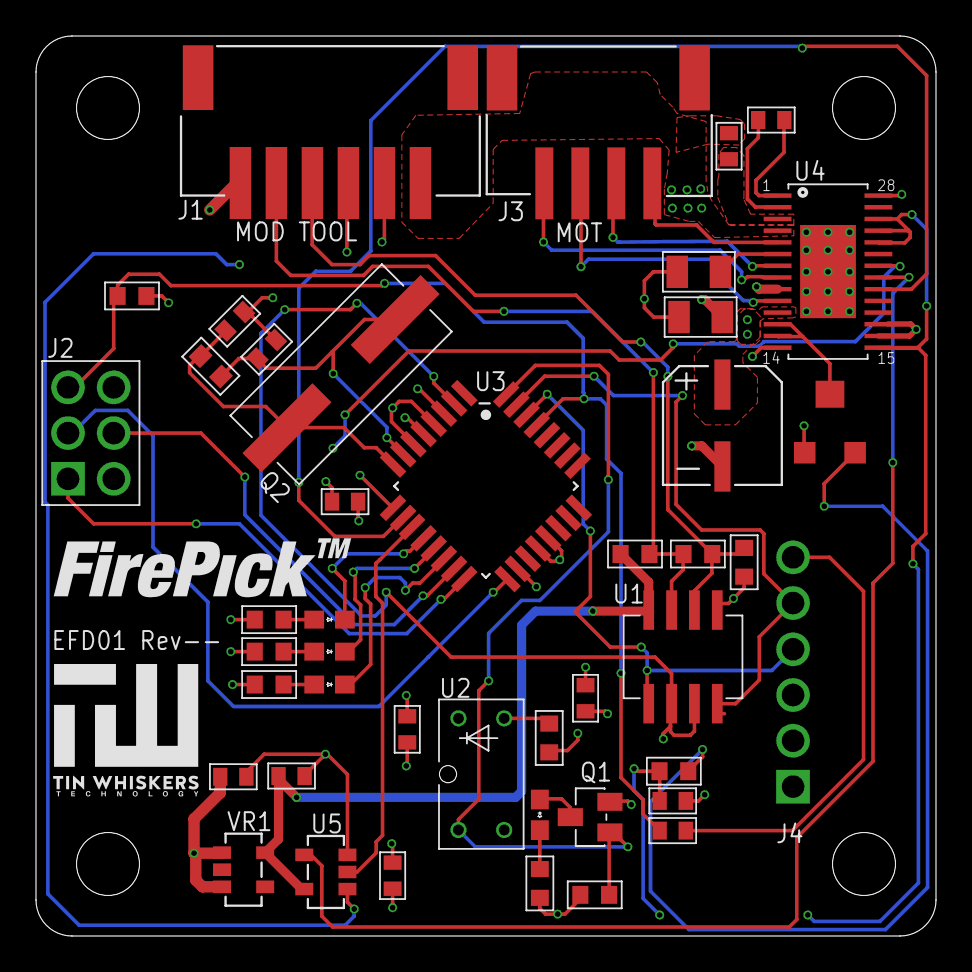
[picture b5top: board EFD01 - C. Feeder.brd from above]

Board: 4 copper layers, 50.0 x 50.0 mm, 46 parts (0 on the bottom side), 43 nets.

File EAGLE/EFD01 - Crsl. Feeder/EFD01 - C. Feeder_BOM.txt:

Mfg Part Num	Description	QTY:	Part References	Price(USD):	Mfg Name	Vendor Part Num	Notes:
UMK107B7104KA-T	Capacitor: 0.1uF, 50V, 10%, X7R	1	C6		Taiyo Yuden	587-1243-1-ND	
RL1206FR-7W0R22L	Resistor: 0.22 Ohm, 0.5W, 1%	2	R5, R6		Yageo	311-.22LYCT-ND	
RC0603FR-071KL	Resistor: 1 kOhm, 0.1W, 1%	3	R3, R4, R11		Yageo	311-1.00KHRCT-ND	
RC0603FR-071ML	Resistor: 1 Mohm, 0.1W, 5%	1	R8		Yageo	311-1.00MHRCT-ND	
UMK107AB7105KA-T	Capacitor, 1uF, 50V, 10%	3	C3, C7, C8		Taiyo Yuden	587-3247-1-ND	
RC0603FR-0710KL	Resistor: 10 kOhm, 0.1W, 1%	2	R9, R12		Yageo	311-10.0KHRCT-ND	
TC33X-2-103E	Potentiometer: Trim, 10 kOhm, 0.1W, 25%	1	R1		Bourns Inc.	TC33X-103EDKR-ND	
GRM188R71H103KA01D	Capacitor: 10nF, 50V, 10%, X7R	1	C1		Murata	490-1512-1-ND	
GRM1885C1H120FA01J	Capacitor: 12pF, 50V, 1%, C0G	2	C4, C5		Murata	490-10705-1-ND	
HCM4916000000ABJT	Crystal Oscillator: 16MHz, 18pF, SMD	1	Q2		Citizen FM	300-6134-1-ND	
RC0603FR-0722KL	Resistor: 22 kOhm, 0.1W, 5%	1	R7		Yageo	311-22.0KHRCT-ND	
SN74LVC1G32DBVR	Logic Gate: OR, 1-CH, SOT23-5	1	U5		Texas Instruments	296-9847-1-ND	
RC0603FR-07100RL	Resistor: 100 Ohm, 0.1W, 1%	1	R2		Yageo	311-100HRCT-ND	
UMK107B7104KA-T	Capacitor: 0.1uF, 50V, 10%, X7R	1	C2		Taiyo Yuden	587-1243-1-ND	
RC0603FR-07120RL	Resistor: 120 Ohm, 0.1W, 1%	1	R10		Yageo	311-120HRCT-ND	
ATMEGA328-AUR	Microprocessor: AVR, 20MHz, 8-Bit Core	1	U3		Atmel	ATMEGA328-AURCT-ND	
BSS138	MOSFET: N-Ch, 50V, 220mA, SOT-23	1	Q1		Fairchild Semiconductor	BSS138CT-ND	
DRV8825PWPR	Motor Driver: Bipolar, Stp/Dir, 1/32, 2.5A	1	U4		Texas Instruments	296-29503-1-ND	
S6B-PH-SM4-TB(LF)(SN)	Connector: 2.0mm (JST), SMT, R/A, 6-POS(M)	1	J4		JST	455-1753-1-ND	
SML-D12M8WT86	LED: YW/GN, Diffused, 2.2V, 20mA	1	LED1		Rohm	511-1578-1-ND	
S6B-PH-SM4-TB(LF)(SN)	Connector: 2.0mm (JST), SMT, R/A, 6-POS(M)	1	J1		JST	455-1753-1-ND	
S4B-PH-SM4-TB(LF)(SN)	Connector: 2.0mm (JST), SMT, R/A, 4-POS(M)	1	J3		JST	455-1751-1-ND	
SP3485	Transceiver: RS-485 Chip	1	U1		EXAR	1016-1817-1-ND	
67996-206HLF	Connector: Header, 0.1ﾔ, 6-Pin, Male, Thru-Hole	1	J2		FCI	609-3210-ND	
TC1015-3.3VCT713	Voltage Reg(LDO): Vi=6V, Vo=3.3V, Io=0.1A	1	VR1		Microchip Tech.	TC1015-3.3VCT713CT-ND	
TCST1030	Optical Sensor: 3.1mm Slot, Thru-Hole, Trans	1	U2		Vishay	TCST1030-ND
